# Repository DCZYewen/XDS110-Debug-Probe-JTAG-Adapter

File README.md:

# XDS110-Debug-Probe-JTAG-Adapter
JTAG Adapter board for TI-20 JTAG header.

这是一个将TI-20 JTAG接口转接为TI-14、ARM Cortex Debug 10P、ARM Serial Wire Debug and XH2.54 UART Jack.

由于一些在设计时没考虑到的线序问题，如果您需要使用常用的IDC 20Pin JTAG排线，请将TI-20 JTAG接口的简牛插座焊接在反面如图所示。

该转接板已在Texas Instrument Code Composer Studio 和 Keil MDK 和 VisualGDB环境下测试通过，可以正常仿真目标器件。

如果对DIY 一个XDS110探针刚兴趣，可以移步[OSHWHub](https://oshwhub.com/dczyewen/xds110-debug-probe)，制作您自己的XDS110探针。该设计具有标准的TI-20 JTAG Header， 可以仿真绝大多数ARM内核处理器以及TI DSP、mmWave Soc、 Wireless Socs。 详情请见[TI的产品手册](https://software-dl.ti.com/ccs/esd/documents/xdsdebugprobes/emu_xds110.html)。

## 效果图

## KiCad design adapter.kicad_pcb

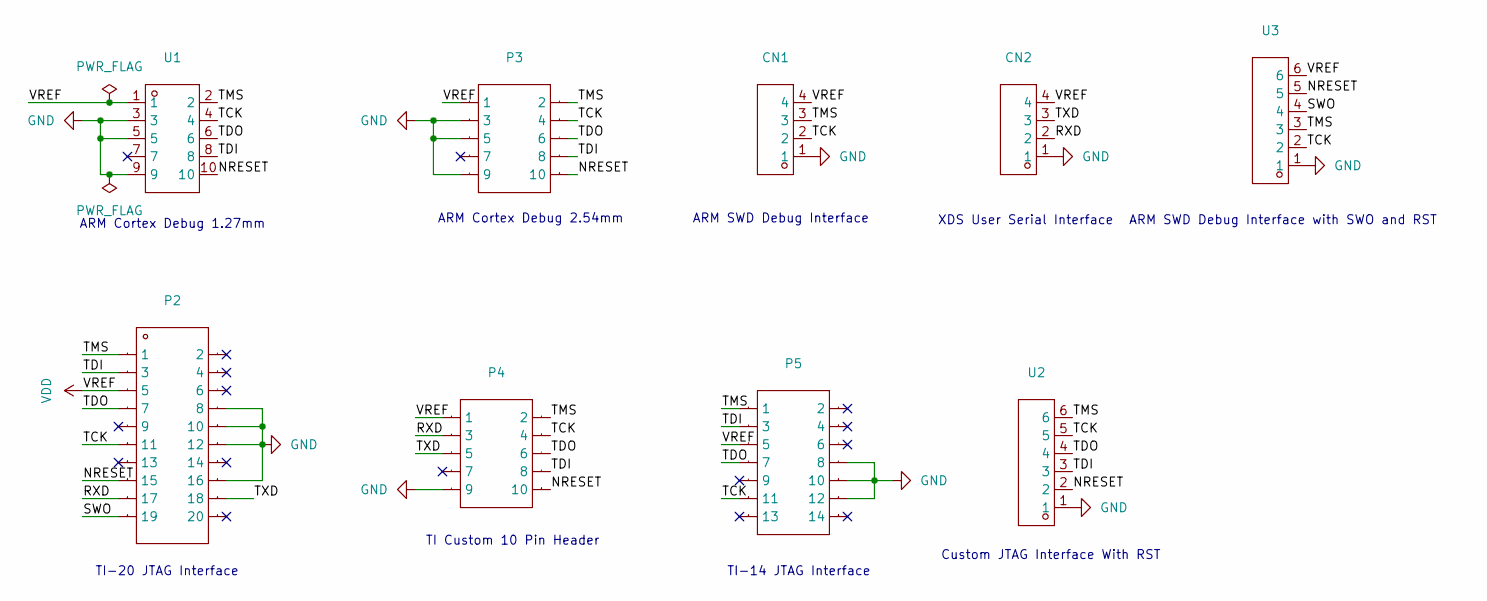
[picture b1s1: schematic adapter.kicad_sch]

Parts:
CN1, CN2: CONN-TH_4P-P2.50_4PIN; Manufacturer Part ZX-XH2.54-4PZZ; LCSC Part Name ZX-XH2.54-4PZZ
P2: IDC-TH_20P-P2.54-V-R2-C10-S2.54; Manufacturer Part 2.54-2*10P简牛; LCSC Part Name 2.54mm 排数:2
P3, P4: IDC-TH_10P-P2.54_C5665; Manufacturer Part 2.54-2*5P简牛; LCSC Part Name 2.54mm 2x5P 排数:2 每排P数:5
P5: IDC-TH_14P-P2.54-V-R2-C7-S2.54; Manufacturer Part 2.54-2*7P简牛; LCSC Part Name 2.54mm 2x7P 排数:2 每排P数:7
U1: CONN-SMD_5P-P1.27_IDC1.27-US2S-5A; Manufacturer Part IDC1.27-US2S-5A; LCSC Part Name 间距1.27 双排 贴片 双向垂直 2*5P 简牛
U2, U3: CONN-TH_6P-P2.50_ZX-XH2.54-6PZZ; Manufacturer Part ZX-XH2.54-6PZZ; LCSC Part Name ZX-XH2.54-6PZZ

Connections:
/NRESET: P2.15, P3.10, P4.10, U1.10, U2.2, U3.5
/RXD: CN2.2, P2.17, P4.3
/SWO: P2.19, U3.4
/TCK: CN1.2, P2.11, P3.4, P4.4, P5.11, U1.4, U2.5, U3.2
/TDI: P2.3, P3.8, P4.8, P5.3, U1.8, U2.3
/TDO: P2.7, P3.6, P4.6, P5.7, U1.6, U2.4
/TMS: CN1.3, P2.1, P3.2, P4.2, P5.1, U1.2, U2.6, U3.3
/TXD: CN2.3, P2.18, P4.5
GND: CN1.1, CN2.1, P2.8, P2.10, P2.12, P2.16, P3.3, P3.5, P3.9, P4.9, P5.8, P5.10, P5.12, U1.3, U1.5, U1.9, U2.1, U3.1
VDD: CN1.4, CN2.4, P2.5, P3.1, P4.1, P5.5, U1.1, U3.6

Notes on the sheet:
Custom JTAG Interface With RST
TI-20 JTAG Interface
TI-14 JTAG Interface
ARM SWD Debug Interface with SWO and RST
ARM SWD Debug Interface
ARM Cortex Debug 1.27mm
ARM Cortex Debug 2.54mm
XDS User Serial Interface
TI Custom 10 Pin Header

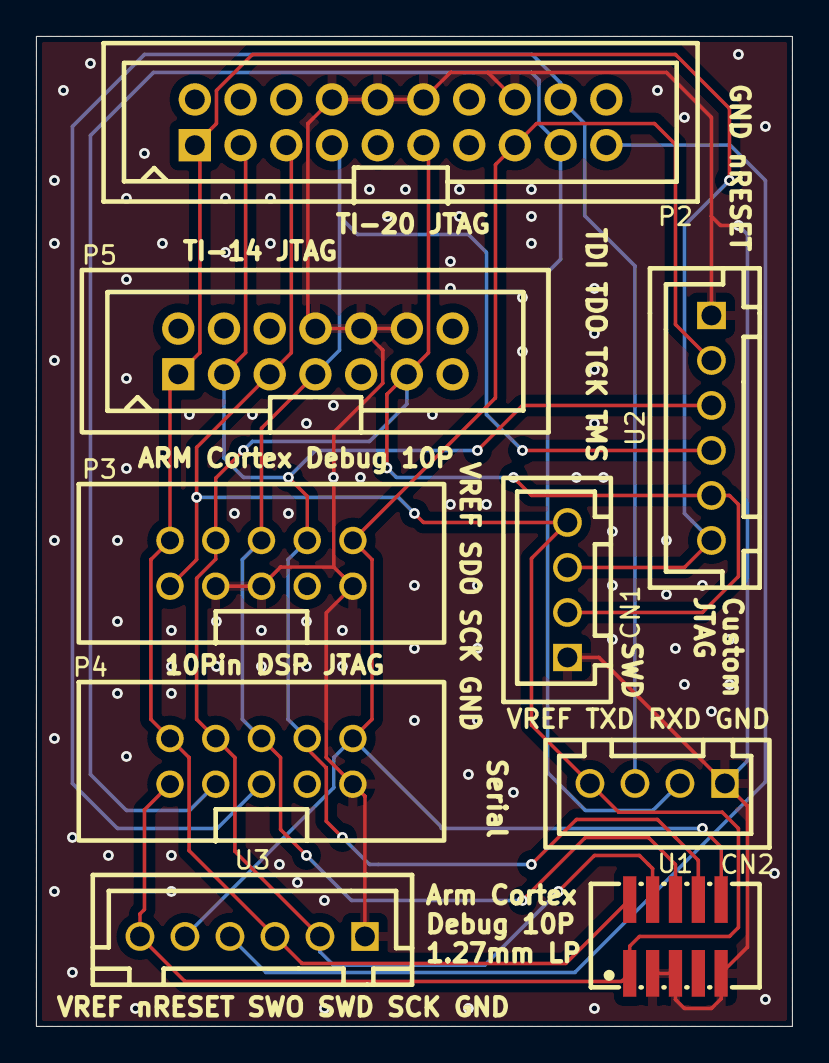
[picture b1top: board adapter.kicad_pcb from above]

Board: 2 copper layers, 42.0 x 55.0 mm, 9 parts (0 on the bottom side), 10 nets.

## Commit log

2024-08-31 Adding design files
